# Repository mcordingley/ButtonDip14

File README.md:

# ButtonDip14
Active-Low RC Button Debounce Board

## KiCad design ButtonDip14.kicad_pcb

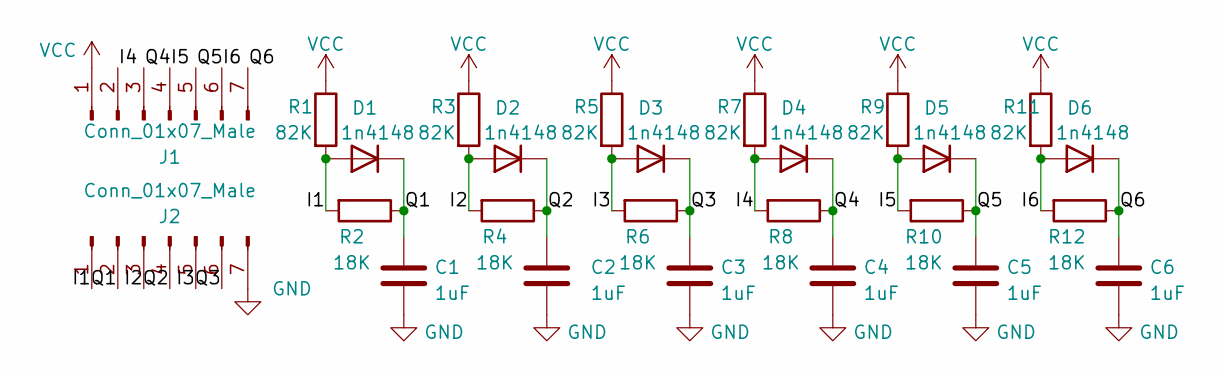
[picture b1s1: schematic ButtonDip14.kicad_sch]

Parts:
C1, C2, C3, C4, C5, C6: 1uF; C_0603_1608Metric
D1, D2, D3, D4, D5, D6: 1n4148; D_0603_1608Metric
J1, J2: Conn_01x07_Male; PinHeader_1x07_P2.54mm_Vertical
R1, R3, R5, R7, R9, R11: 82K; R_0603_1608Metric
R2, R4, R6, R8, R10, R12: 18K; R_0603_1608Metric

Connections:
/I1: D1.2 (A), J2.1, R1.2, R2.2
/I2: D2.2 (A), J2.3, R3.2, R4.2
/I3: D3.2 (A), J2.5, R5.2, R6.2
/I4: D4.2 (A), J1.2, R7.2, R8.2
/I5: D5.2 (A), J1.4, R9.2, R10.2
/I6: D6.2 (A), J1.6, R11.2, R12.2
/Q1: C1.1, D1.1 (K), J2.2, R2.1
/Q2: C2.1, D2.1 (K), J2.4, R4.1
/Q3: C3.1, D3.1 (K), J2.6, R6.1
/Q4: C4.1, D4.1 (K), J1.3, R8.1
/Q5: C5.1, D5.1 (K), J1.5, R10.1
/Q6: C6.1, D6.1 (K), J1.7, R12.1
GND: C1.2, C2.2, C3.2, C4.2, C5.2, C6.2, J2.7
VCC: J1.1, R1.1, R3.1, R5.1, R7.1, R9.1, R11.1

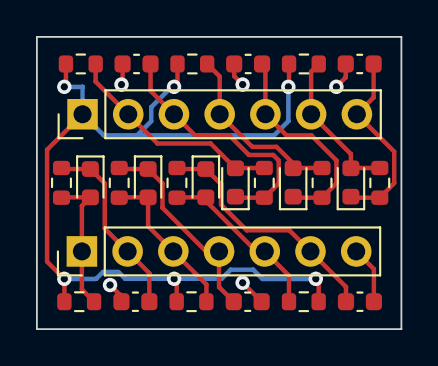
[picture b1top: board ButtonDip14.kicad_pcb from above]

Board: 2 copper layers, 20.2 x 16.2 mm, 26 parts (0 on the bottom side), 14 nets.

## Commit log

2023-08-13 Import.
